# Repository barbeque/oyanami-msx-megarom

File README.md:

# Oyanami
TODO: Overview

This project was built as part of a [Leaded Solder blog](https://www.leadedsolder.com/) entry.

Articles so far about this project:
 - [Oya, I've heard of Mega-ROMs](https://www.leadedsolder.com/2024/09/03/msx-megarom-oyanami.html)

If it's useful to you, please consider supporting the blog through [Patreon](https://patreon.com/leadedsolder) or [Ko-Fi](https://ko-fi.com/leadedsolder). All money goes directly to future projects like this.

## Build It Yourself!
The Oyanami board is open-source. You can grab the Gerber files from [the Releases page](https://github.com/barbeque/oyanami-msx-megarom/releases) and send those to a fabricator of your choice.

Recommended settings: 

 - ENIG or Hard Gold finishing
 - Beveled or chamfered edge connector

## Known Working Games
 - 1942 (MSX2 version only)
 - Arkanoid 2 - Revenge of DOH
 - Ashguine Story I
 - Bubble Bobble
 - Contra (MSX2; CRC32: 4e82660d)
 - Cyborg Z
 - Digital Devil Story
 - Dragon Buster
 - Dragon Quest 1 (both MSX1, MSX2 versions)
 - Druid
 - F1 Spirit
 - Family Billiards
 - Fantasy Zone 1
 - Final Zone Wolf
 - Ganbare Goemon
 - Gangjeol Robocop
 - Genesis - Dawn of a New Day
 - Hai No Majutsushi
 - Hinotori
 - King Kong 2
 - King's Valley 2 Edit Contest Edition
 - King's Valley 2 (MSX2 only)
 - Metal Gear (CRC32: e85c5731)
 - Mr. Ninja Ashura's Chapter
 - Nemesis (CRC32: 4dfcc009)
 - Nemesis 2
 - Parodius
 - Pengo
 - Penguin Adventure
 - Pennant Race
 - Return of Jelda
 - Salamander
 - Spy vs. Spy II (64kB Konami-mapper version)
 - Seikima 2 Special - Tetsuji
 - Street Master
 - Super Bioman 4
 - Super Boy 3
 - Super Runner
 - Tengoku Yoitoko - Heaven
 - The Fairyland Story
 - The Fantasm Soldier Valis
 - The Maze of Galious: Knightmare 2
 - Topple Zip MSX2
 - Treasure of USAS (MSX2)
 - Vampire Killer (MSX2)
 - Wonsiin
 - Young Sherlock: Legacy of Doyle

This is an incomplete list, please submit pull requests for any other games you have tested.

## Bill of Materials

| Position | Component     | Digi-Key link      | Comments  |
|----------|---------------|--------------------|-----------|
| U1       | SST39SF040 DIP EEPROM | | |
| U3       | 74LS670 DIP | | Do not use ALS, see below |
| U4       | 74LS02 DIP | | |
| C...     | 0.1µF through-hole ceramic capacitor | | |
| RN1      | 10kΩ x 8 (9-pin SIP) resistor network | | |
| SW1      | 2-pin DIP switch | | |

I also recommend getting a case for the PCB from somewhere like [Retro Game Restore](https://retrogamerestore.com/store/msx_cart_shell).

Beware! Using socketed ICs may not leave enough vertical height for a standard Konami-style cartridge case to close.

74ALS670 has been reported not to work with MSX Turbo-R systems. Please use only the LS variant.

## Version History
### v1.2: In development
Still in development. Adds write-enable pin to ROM to support in-MSX reflashing.

### v1.1: July 2024
Initial working version. Supports read-only games.

## Special Thanks
 - bsittler for the help and inspiration to get this figured out;
 - Pax for CRC32s;
 - Annual_Bottle_4639 on Reddit for testing additional games

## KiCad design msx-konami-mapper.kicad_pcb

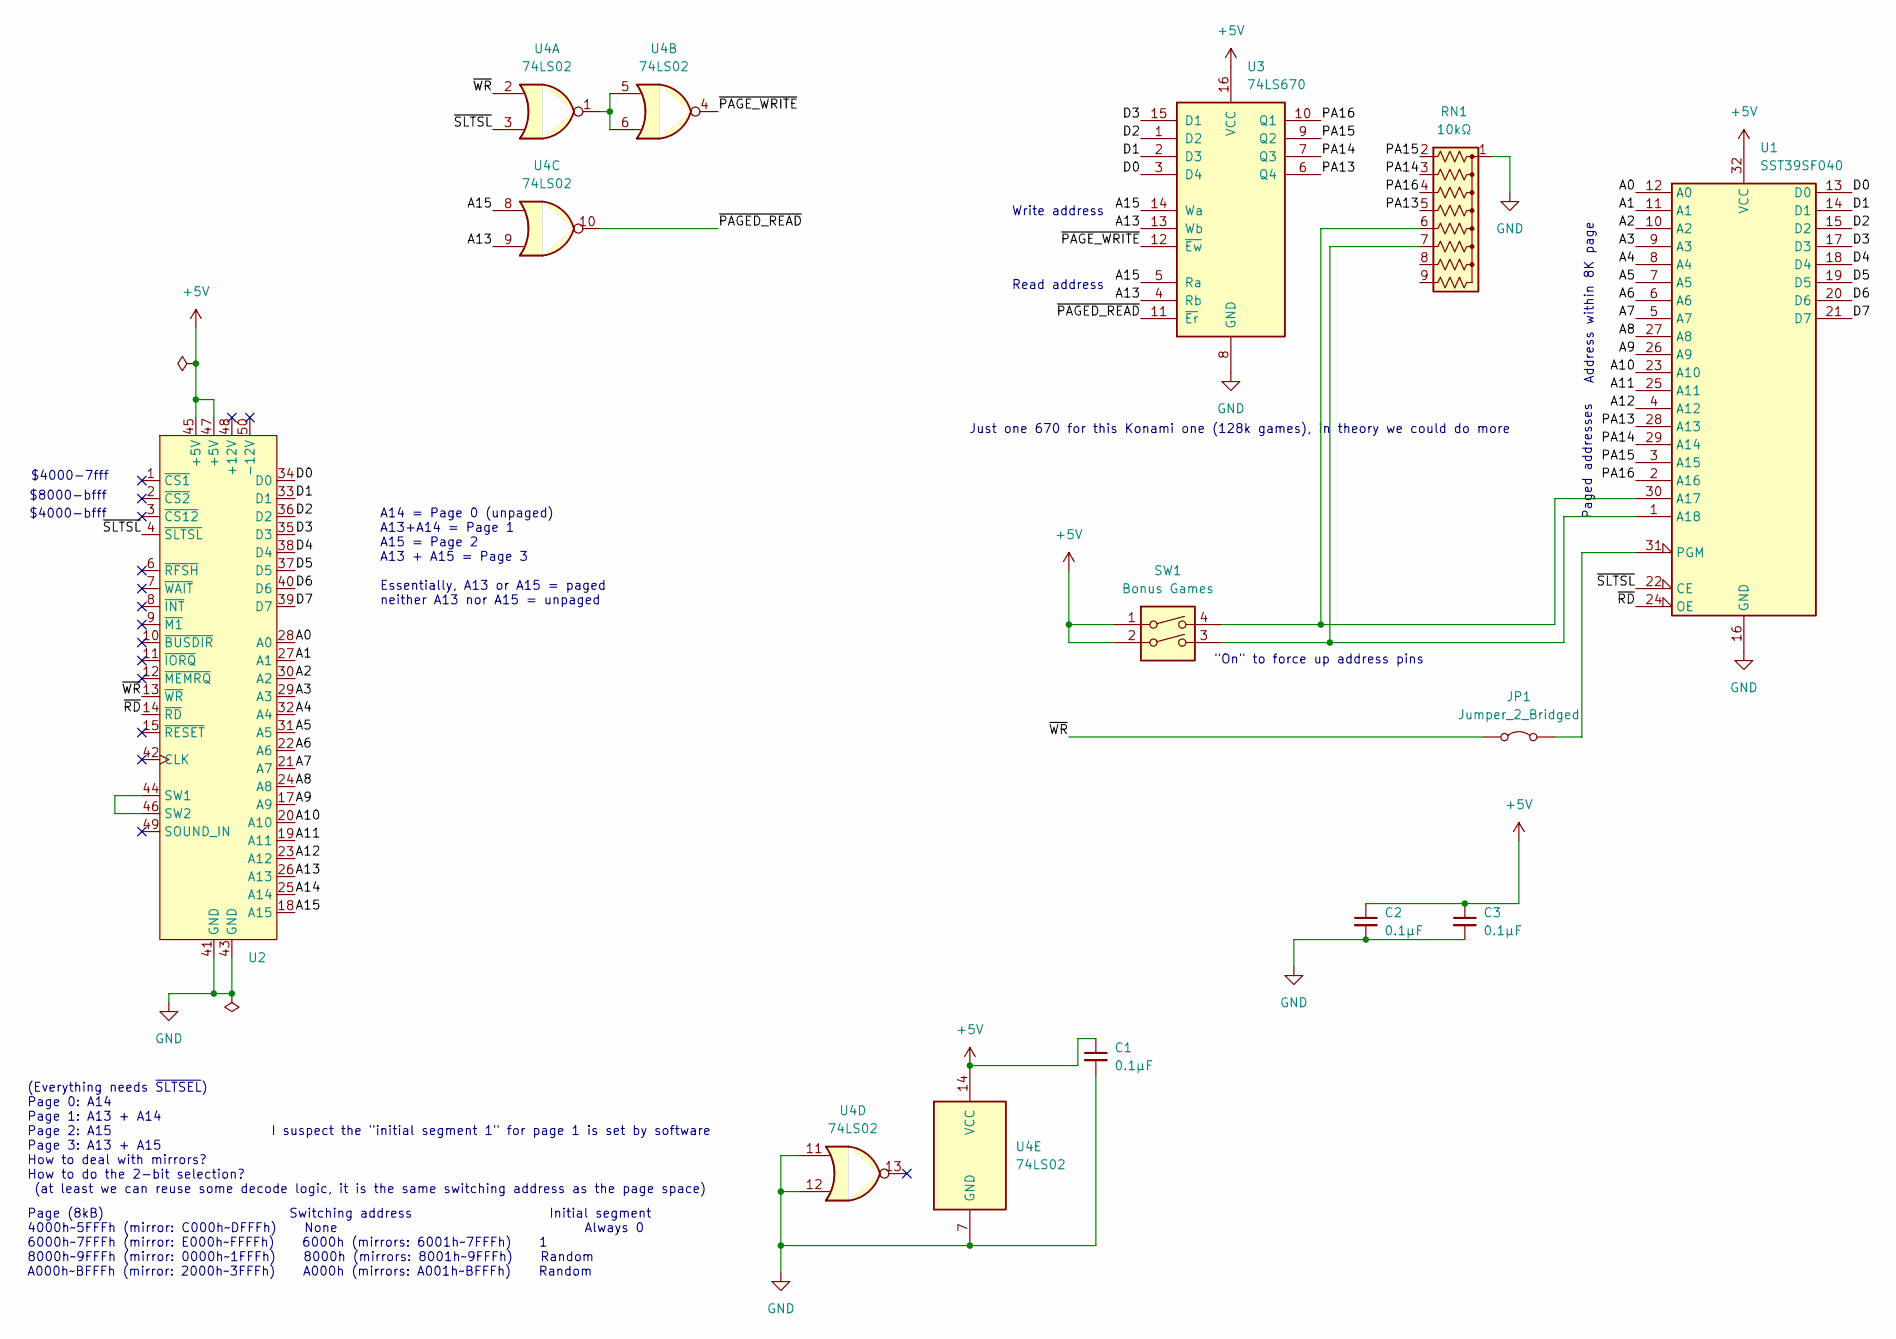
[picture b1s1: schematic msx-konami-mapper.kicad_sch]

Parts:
C1: 0.1µF; C_Disc_D3.8mm_W2.6mm_P2.50mm
C2, C3: 0.1µF; C_Disc_D3.8mm_W2.6mm_P2.50mm; DigiKey 399-9776-ND
JP1: Jumper_2_Bridged; SolderJumper-2_P1.3mm_Bridged_RoundedPad1.0x1.5mm
RN1: 10kΩ; R_Array_SIP9; DigiKey 4609X-101-103LF-ND
SW1: Bonus Games; SW_DIP_SPSTx02_Slide_9.78x7.26mm_W7.62mm_P2.54mm; DigiKey 2223-DS01-254-L-02BE-ND
U1: SST39SF040; DIP-32_W15.24mm_Socket_LongPads; DigiKey SST39SF040-70-4C-PHE-ND
U2: Cartridge
U3: 74LS670; DIP-16_W7.62mm_Socket_LongPads; DigiKey 296-34025-5-ND
U4: 74LS02; DIP-14_W7.62mm_Socket_LongPads; DigiKey 296-1627-5-ND

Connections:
+5V: C1.1, C2.1, C3.1, SW1.1, SW1.2, U1.32 (VCC), U2.45 (+5V), U2.47 (+5V), U3.16 (VCC), U4.14 (VCC)
/A0: U1.12 (A0), U2.28 (A0)
/A1: U1.11 (A1), U2.27 (A1)
/A2: U1.10 (A2), U2.30 (A2)
/A3: U1.9 (A3), U2.29 (A3)
/A4: U1.8 (A4), U2.32 (A4)
/A5: U1.7 (A5), U2.31 (A5)
/A6: U1.6 (A6), U2.22 (A6)
/A7: U1.5 (A7), U2.21 (A7)
/A8: U1.27 (A8), U2.24 (A8)
/A9: U1.26 (A9), U2.17 (A9)
/A10: U1.23 (A10), U2.20 (A10)
/A11: U1.25 (A11), U2.19 (A11)
/A12: U1.4 (A12), U2.23 (A12)
/A13: U2.26 (A13), U3.4 (Rb), U3.13 (Wb), U4.9
/A14: U2.25 (A14)
/A15: U2.18 (A15), U3.5 (Ra), U3.14 (Wa), U4.8
/D0: U1.13 (D0), U2.34 (D0), U3.3 (D4)
/D1: U1.14 (D1), U2.33 (D1), U3.2 (D3)
/D2: U1.15 (D2), U2.36 (D2), U3.1 (D2)
/D3: U1.17 (D3), U2.35 (D3), U3.15 (D1)
/D4: U1.18 (D4), U2.38 (D4)
/D5: U1.19 (D5), U2.37 (D5)
/D6: U1.20 (D6), U2.40 (D6)
/D7: U1.21 (D7), U2.39 (D7)
/PA13: RN1.5 (R4), U1.28 (A13), U3.6 (Q4)
/PA14: RN1.3 (R2), U1.29 (A14), U3.7 (Q3)
/PA15: RN1.2 (R1), U1.3 (A15), U3.9 (Q2)
/PA16: RN1.4 (R3), U1.2 (A16), U3.10 (Q1)
/~PAGED_READ: U3.11 (~Er), U4.10
/~PAGE_WRITE: U3.12 (~Ew), U4.4
/~RD: U1.24 (OE), U2.14 (~RD)
/~SLTSL: U1.22 (CE), U2.4 (~SLTSL), U4.3
/~WR: JP1.1 (A), U2.13 (~WR), U4.2
GND: C1.2, C2.2, C3.2, RN1.1 (common), U1.16 (GND), U2.41 (GND), U2.43 (GND), U3.8 (GND), U4.7 (GND), U4.11, U4.12
unnamed: JP1.2 (B), U1.31 (PGM)
unnamed: RN1.6 (R5), SW1.4, U1.30 (A17)
unnamed: RN1.7 (R6), SW1.3, U1.1 (A18)
unnamed: U2.44 (SW1), U2.46 (SW2)
unnamed: U4.1, U4.5, U4.6

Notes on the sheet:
Paged addresses
Write address
Address within 8K page
A14 = Page 0 (unpaged) A13+A14 = Page 1 A15 = Page 2 A13 + A15 = Page 3 Essentially, A13 or A15 = paged neither A13 nor A15 = unpaged
$8000-bfff
$4000-7fff
Read address
$4000-bfff
Page (8kB) Switching address Initial segment 4000h~5FFFh (mirror: C000h~DFFFh) None Always 0 6000h~7FFFh (mirror: E000h~FFFFh) 6000h (mirrors: 6001h~7FFFh) 1 8000h~9FFFh (mirror: 0000h~1FFFh) 8000h (mirrors: 8001h~9FFFh) Random A000h~BFFFh (mirror: 2000h~3FFFh) A000h (mirrors: A001h~BFFFh) Random
"On" to force up address pins
I suspect the "initial segment 1" for page 1 is set by software
(Everything needs ~{SLTSEL}) Page 0: A14 Page 1: A13 + A14 Page 2: A15 Page 3: A13 + A15 How to deal with mirrors? How to do the 2-bit selection? (at least we can reuse some decode logic, it is the same switching address as the page space)
Just one 670 for this Konami one (128k games), in theory we could do more

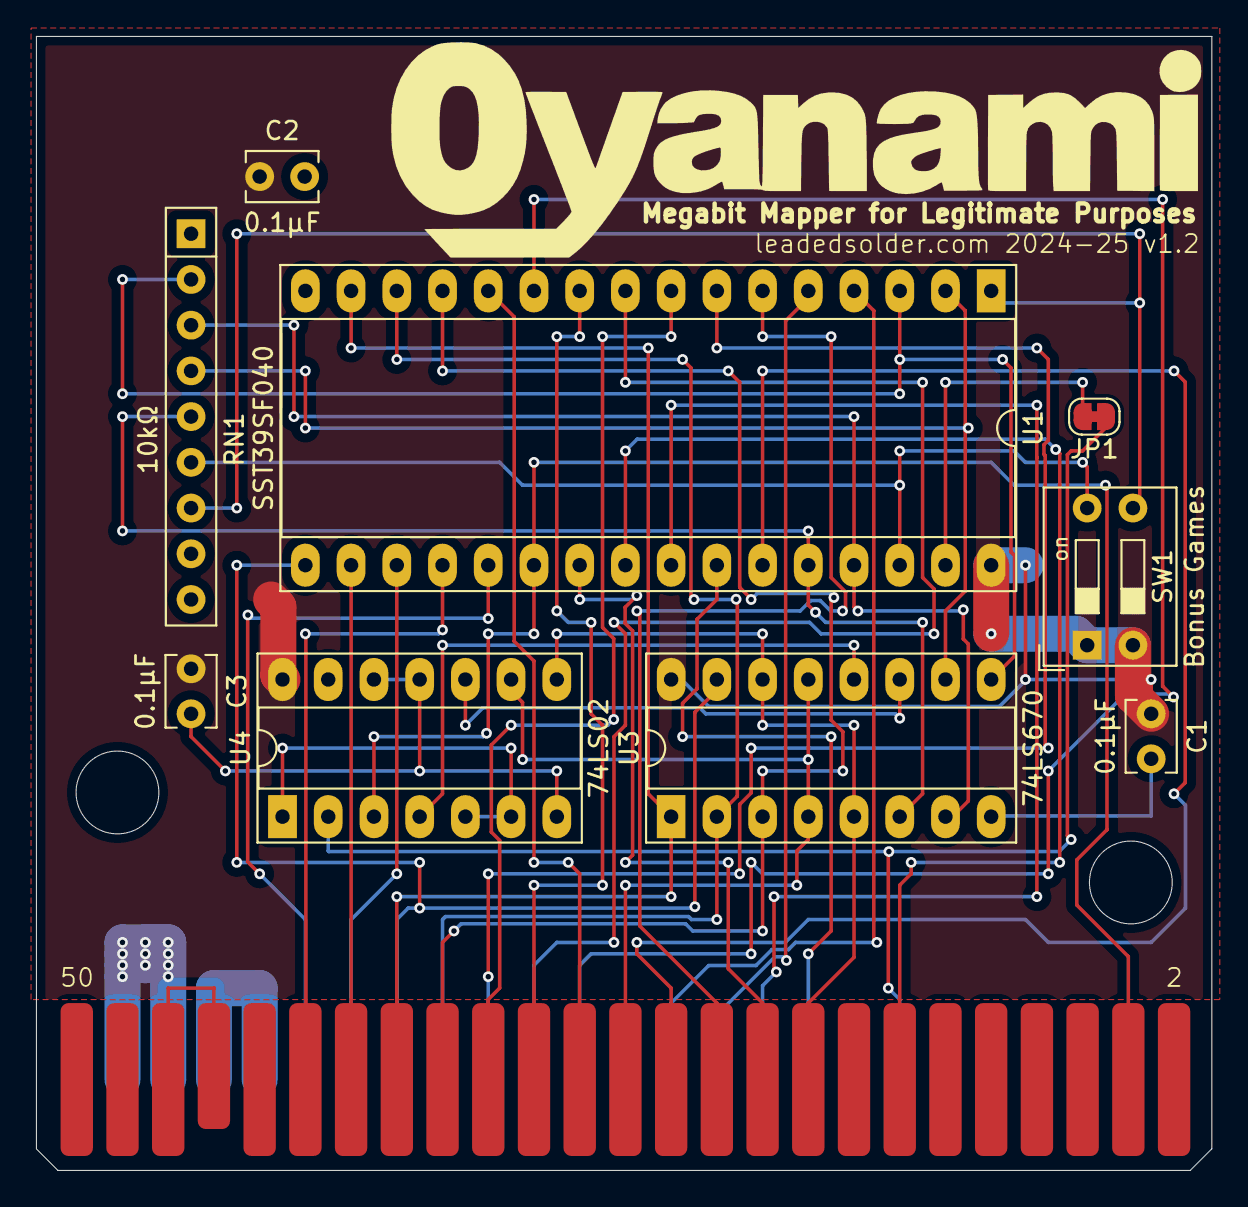
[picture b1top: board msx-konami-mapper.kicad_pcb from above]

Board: 2 copper layers, 65.3 x 63.0 mm, 10 parts (0 on the bottom side), 39 nets.

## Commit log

2024-06-27 Oyanami logo, rough board dims
2024-06-27 Placed EPROM, I may regret this
2024-06-28 Edge connector
2024-06-28 Put the connector the right way around, dimwit
2024-06-28 Data pins
2024-06-28 Pins
2024-06-28 Super gross data bus I'll probably tear up later
2024-06-28 Wipe the data bus after all
2024-06-28 Disable programming for v1.0
2024-06-28 The mysteries of decoding
2024-06-28 Starting to puzzle this out
2024-06-28 Notes to self
2024-06-28 Experimental dual-game select
2024-06-28 Yes, I need another 670
2024-06-28 Driving 8 bits of pages
2024-06-28 Undoing bad work
2024-06-28 I think this works
2024-06-28 Routed
2024-07-04 V1.1 begins... worried about C1 being too close to mounting hole
2024-07-10 Widen holes to fit into case better
2024-07-10 Add 'rear' tag
2024-07-14 ignore autosave
2024-07-14 Making a test rom
2024-07-15 Pull-downs for '670 output
2024-07-15 Fix DIP switch being backward
2024-07-15 Prepare v1.1 for release
2024-07-15 Remove some parts
2024-07-15 Better explainer
2024-07-29 Basic README
2024-07-29 Case warning
2024-10-10 Create LICENSE
2025-01-22 Partial compatibility list from Annual_Bottle_4639 on Reddit
2025-02-03 Prepare for BOM release
2025-02-03 DK part numbers
2025-02-07 Additional compatibility list
2025-02-07 Add CRC
2025-02-07 CRC for Metal Gear
2025-02-07 CRC32 for Contra
2025-03-15 KiCad 9; add WR to ROM; fix +5V weak trace
2025-03-15 History
2025-03-15 Links to articles
2025-03-15 Better CTA
